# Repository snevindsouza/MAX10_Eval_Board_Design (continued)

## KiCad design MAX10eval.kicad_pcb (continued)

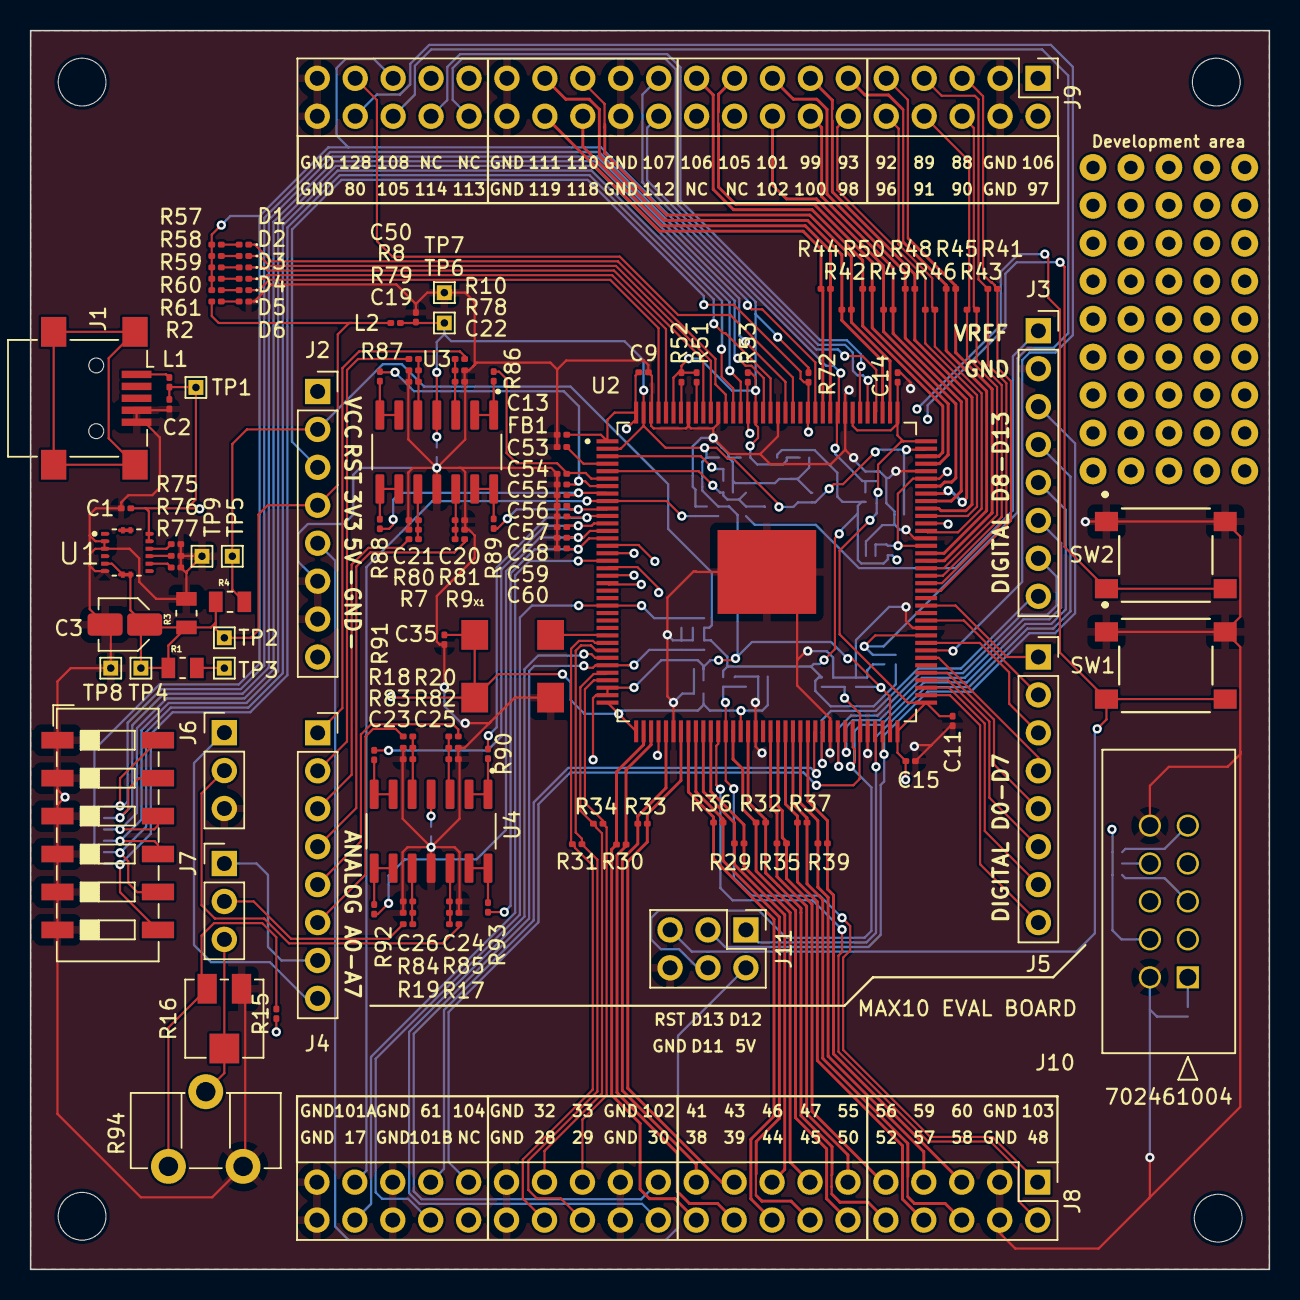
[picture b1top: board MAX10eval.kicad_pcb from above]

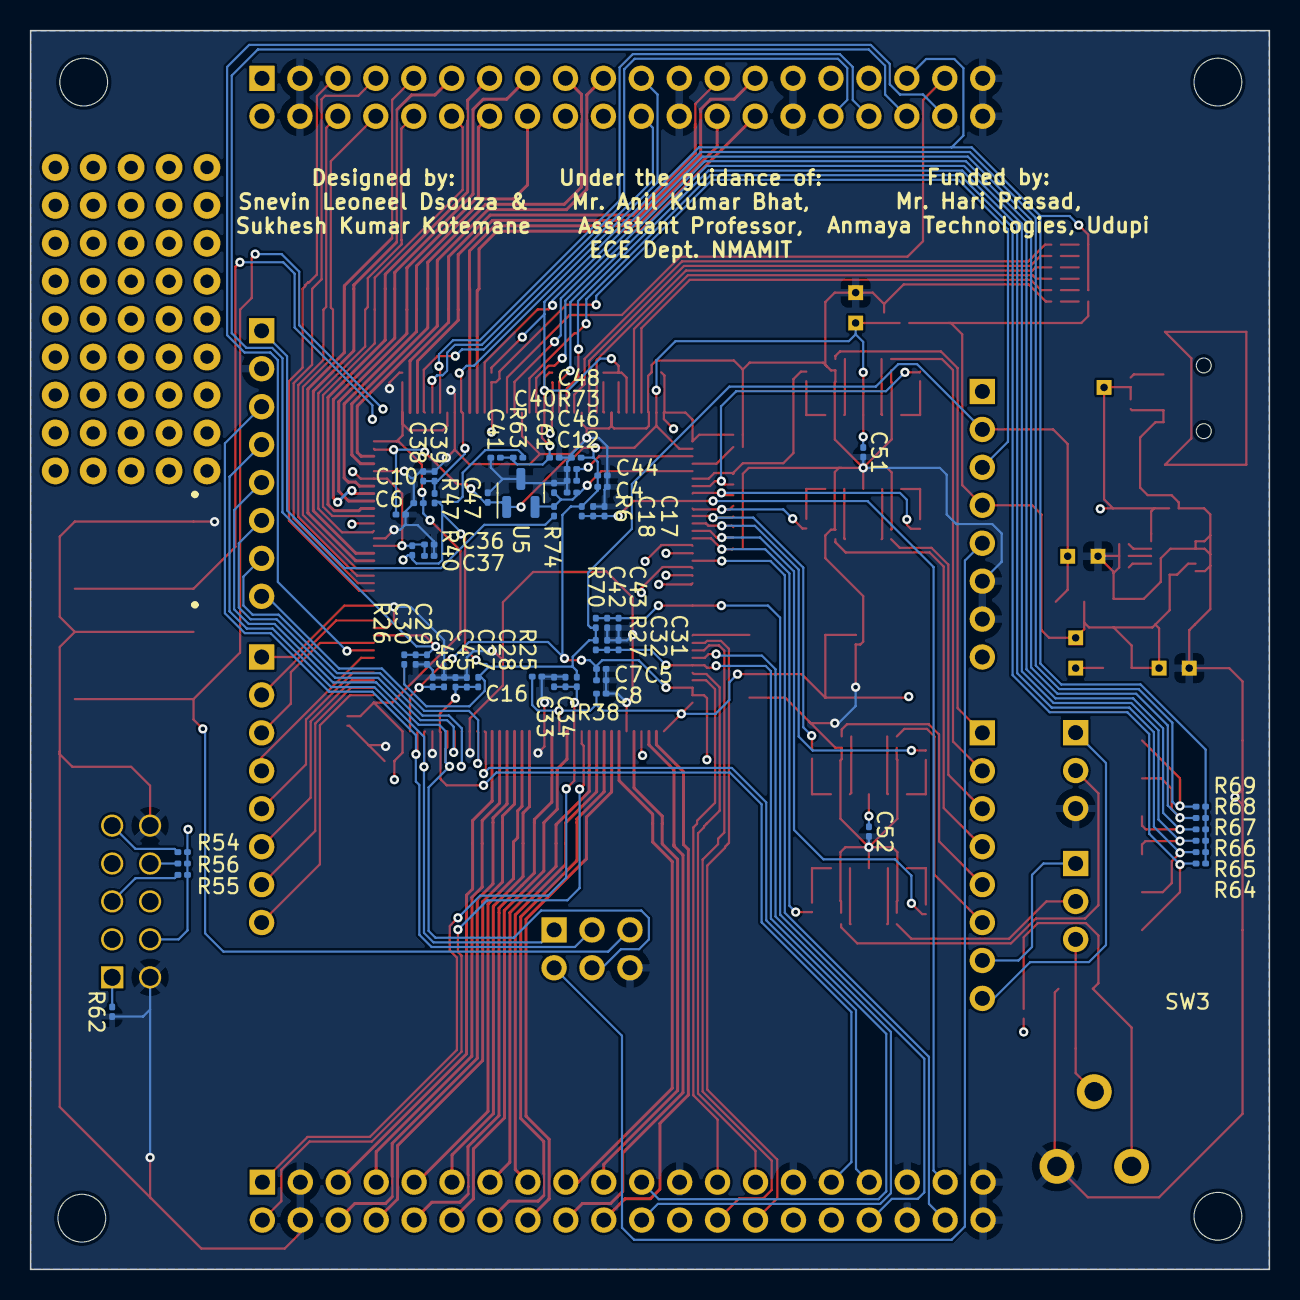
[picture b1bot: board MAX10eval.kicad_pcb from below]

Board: 4 copper layers, 82.9 x 82.9 mm, 186 parts (57 on the bottom side), 148 nets.
